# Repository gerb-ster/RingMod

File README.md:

# YUSynth Ring Modulator

This module is based on the design from YuSynth, found at http://yusynth.net/Modular/EN/RINGMOD/index.html. Nothing really special, just a cool handy ring modulator. The sound sample is created using the sine outputs of two VCO’s.

## Status: Finished

- done: first schematic & board design
- done: breadboard and test
- done: design frontpanel
- done: order PCB and build prototype

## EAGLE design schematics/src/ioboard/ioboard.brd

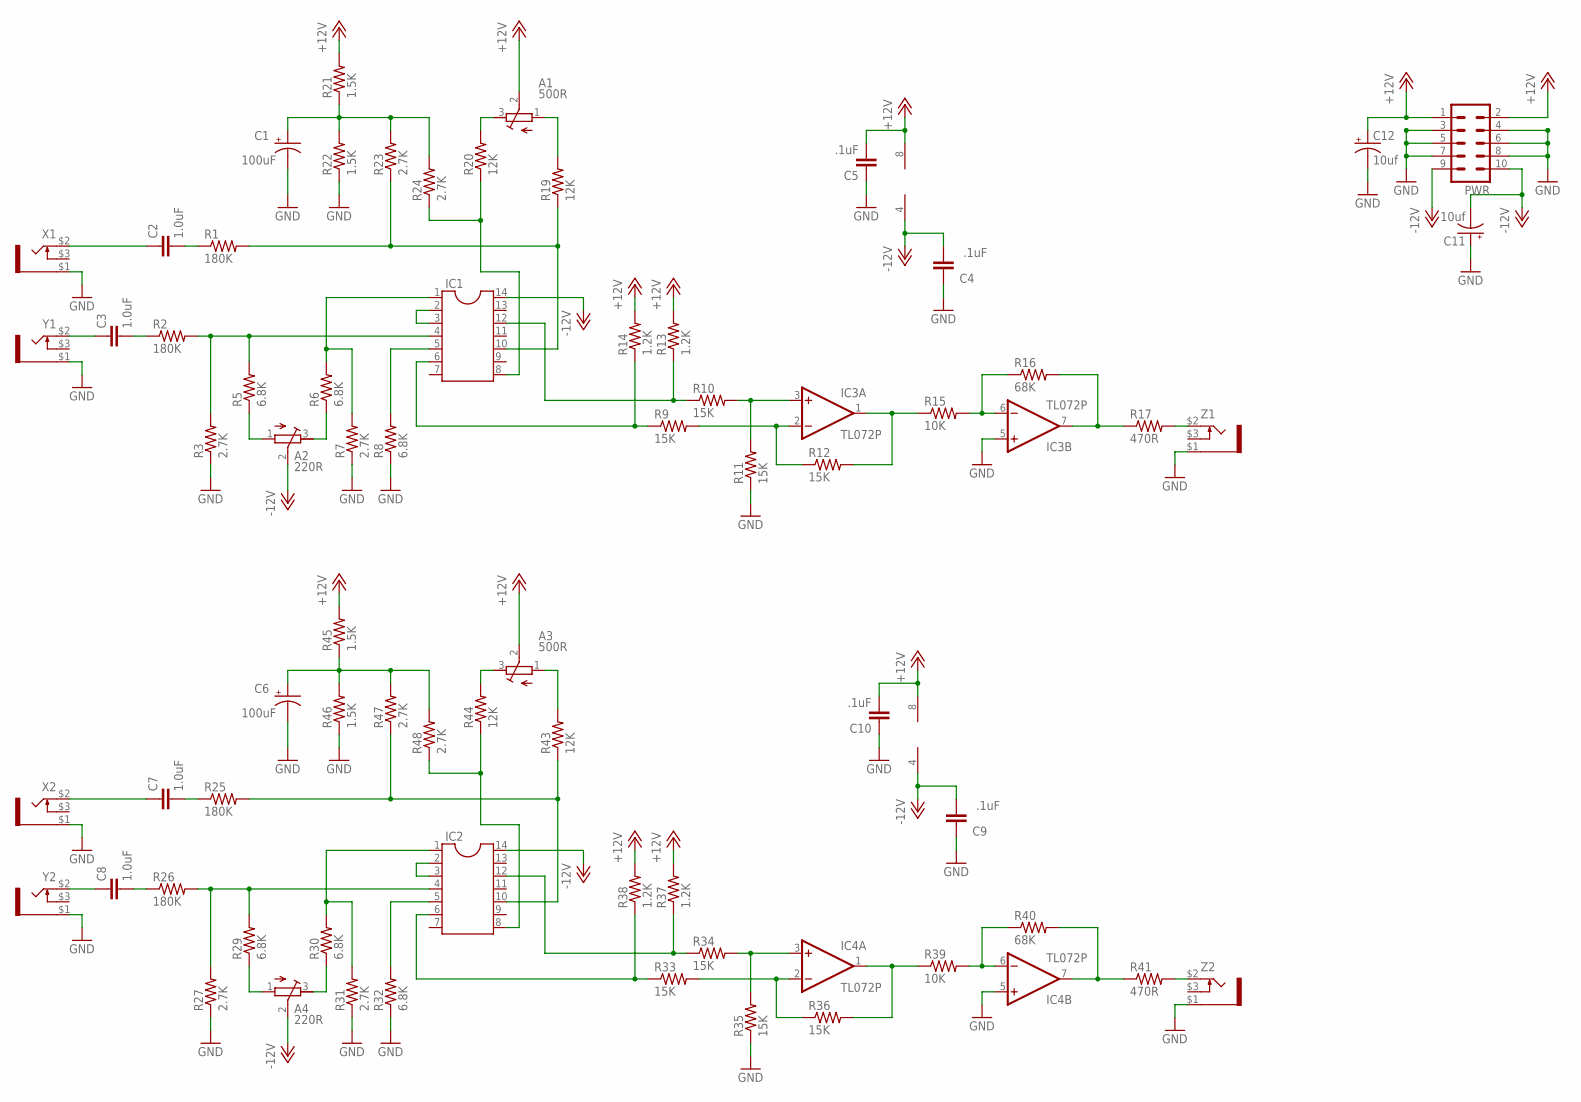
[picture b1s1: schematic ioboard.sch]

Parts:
A1, A3: 500R; RTRIM3296W
A2, A4: 220R; RTRIM3296W
C1, C6: 100uF; E2,5-6
C2, C3, C7, C8: 1.0uF; C050-024X044
C4, C5, C9, C10: .1uF; C050-024X044
C11, C12: 10uf; E2,5-5
IC1, IC2: LM1496
IC3, IC4: TL072P; DIL08
PWR: ML10
R1, R2, R25, R26: 180K; 0207/7
R3, R7, R23, R24, R27, R31, R47, R48: 2.7K; 0207/7
R5, R6, R8, R29, R30, R32: 6.8K; 0207/7
R9, R10, R11, R12, R33, R34, R35, R36: 15K; 0207/7
R13, R14, R37, R38: 1.2K; 0207/7
R15, R39: 10K; 0207/7
R16, R40: 68K; 0207/7
R17, R41: 470R; 0207/7
R19, R20, R43, R44: 12K; 0207/7
R21, R22, R45, R46: 1.5K; 0207/7
X1, X2: PJ-323PJ-323; PJ-323
Y1, Y2: PJ-323PJ-323; PJ-323
Z1, Z2: PJ-323PJ-323; PJ-323

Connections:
+12V: A1.2 (S), A3.2 (S), C5.2, C10.2, C12.+, IC3.8 (V+), IC4.8 (V+), PWR.1, PWR.2, R13.2, R14.2, R21.2, R37.2, R38.2, R45.2
-12V: A2.2 (S), A4.2 (S), C4.2, C9.2, C11.-, IC1.14, IC2.14, IC3.4 (V-), IC4.4 (V-), PWR.9, PWR.10
GND: C1.-, C4.1, C5.1, C6.-, C9.1, C10.1, C11.+, C12.-, IC3.5 (+IN), IC4.5 (+IN), PWR.3, PWR.4, PWR.5, PWR.6, PWR.7, PWR.8, R3.1, R7.1, R8.1, R11.1, R22.1, R27.1, R31.1, R32.1, R35.1, R46.1, X1.$1 (3), X2.$1 (3), Y1.$1 (3), Y2.$1 (3), Z1.$1 (3), Z2.$1 (3)
unnamed: C2.1, X1.$2 (1)
unnamed: C3.1, Y1.$2 (1)
unnamed: C2.2, R1.1
unnamed: C3.2, R2.1
unnamed: IC1.2, IC1.3
unnamed: IC1.4, R2.2, R3.2, R5.2
unnamed: C1.+, R21.1, R22.2, R23.2, R24.2
unnamed: A2.1 (A), R5.1
unnamed: IC1.1, R6.2, R7.2
unnamed: A2.3 (E), R6.1
unnamed: IC1.5, R8.2
unnamed: IC1.6, R9.1, R14.1
unnamed: IC3.2 (-IN), R9.2, R12.1
unnamed: IC1.12, R10.1, R13.1
unnamed: IC3.3 (+IN), R10.2, R11.2
unnamed: IC3.1 (OUT), R12.2, R15.1
unnamed: IC3.6 (-IN), R15.2, R16.1
unnamed: R17.2, Z1.$2 (1)
unnamed: IC3.7 (OUT), R16.2, R17.1
unnamed: A1.3 (E), R20.2
unnamed: IC1.8, R20.1, R24.1
unnamed: A1.1 (A), R19.2
unnamed: IC1.10, R1.2, R19.1, R23.1
unnamed: C7.1, X2.$2 (1)
unnamed: C8.1, Y2.$2 (1)
unnamed: C7.2, R25.1
unnamed: C8.2, R26.1
unnamed: IC2.2, IC2.3
unnamed: IC2.4, R26.2, R27.2, R29.2
unnamed: A4.1 (A), R29.1
unnamed: IC2.1, R30.2, R31.2
unnamed: A4.3 (E), R30.1
unnamed: IC2.5, R32.2
unnamed: IC2.6, R33.1, R38.1
unnamed: IC4.2 (-IN), R33.2, R36.1
unnamed: IC2.12, R34.1, R37.1
unnamed: IC4.3 (+IN), R34.2, R35.2
unnamed: IC4.1 (OUT), R36.2, R39.1
unnamed: IC4.6 (-IN), R39.2, R40.1
unnamed: IC4.7 (OUT), R40.2, R41.1
unnamed: R41.2, Z2.$2 (1)
unnamed: IC2.8, R44.1, R48.1
unnamed: A3.1 (A), R43.2
unnamed: A3.3 (E), R44.2
unnamed: IC2.10, R25.2, R43.1, R47.1
unnamed: C6.+, R45.1, R46.2, R47.2, R48.2

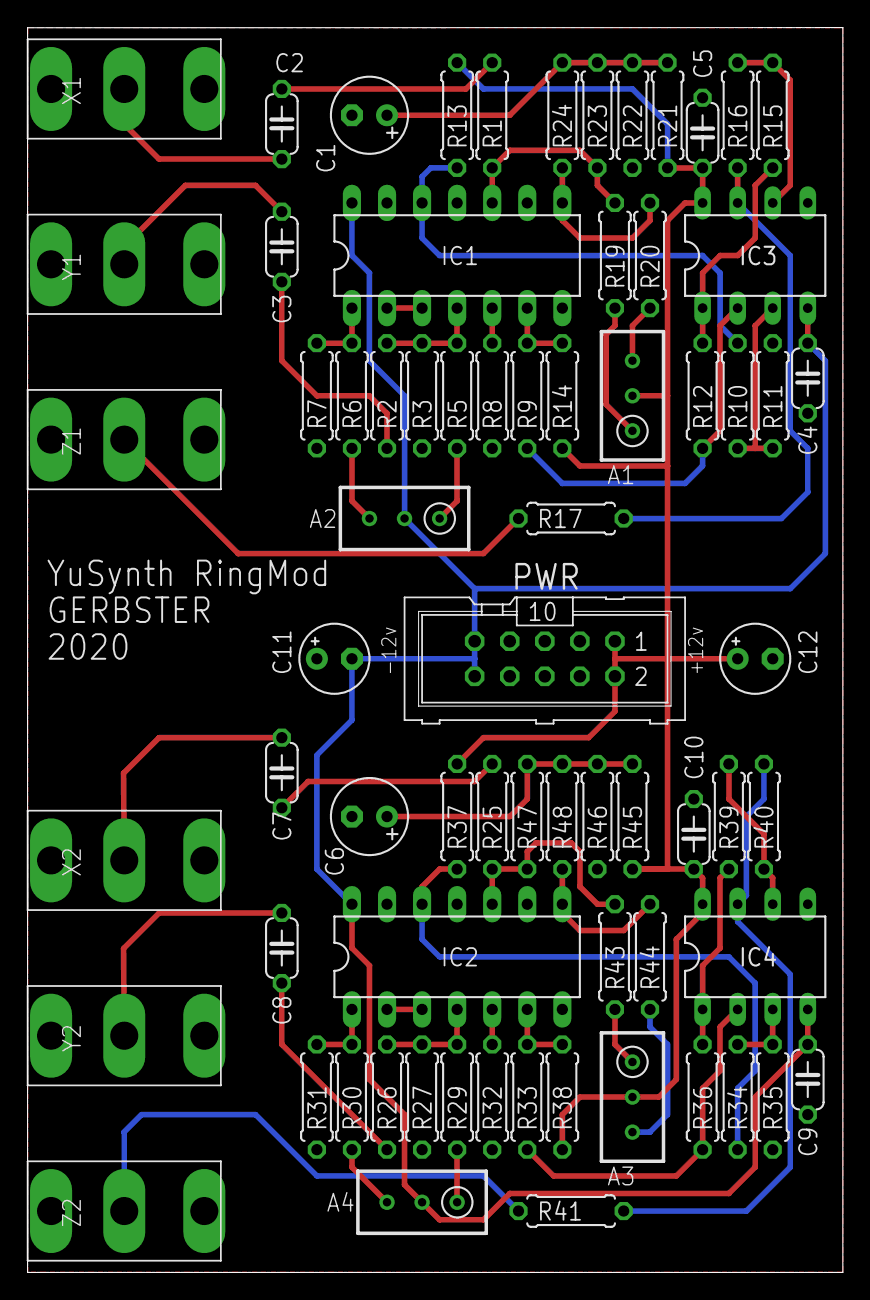
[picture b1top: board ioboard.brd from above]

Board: 2 copper layers, 59.1 x 90.2 mm, 71 parts (0 on the bottom side), 49 nets.

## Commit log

2021-05-06 some files
2021-05-07 Added files & structure
2021-05-10 Added Status
2021-05-11 Added Status & Images
2021-08-06 Updated some schematics and docs
2021-08-10 Fixed some bugs and updated documentation
2022-04-20 Some updates & bugfixes
2022-04-22 Fixed schematics & descriptions
2022-05-17 Updated Firmware
2022-05-18 Updated Faceplates
2022-05-18 Fixed issues
2022-05-21 Fixed schematics
2022-05-28 General updates
